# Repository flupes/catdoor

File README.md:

# catdoor
Cat door opening detection and notification

## First version

Notification of cat entry only (catdoor locked so that the cat can never go out, but always come in). This allows to make sure the cat in inside before dark in case we are coming late home.

### Sensing

Based on a proximity sensor looking down where the door opens. Some reflective on the side of the door allow a ver good signature, sorting out the cat. In fact, test of reflectivity on the cat hairs shows very poor reflection. Tuning the system as been done by observing serveral opening (look in the data directory)

- Microcontroller with ESP8266 Wifi:[Adafruit Feather HUZZAH with ESP8266 WiFi](https://www.adafruit.com/product/2821)
- Breadkout sensor board: [VCNL4010 Proximity/Light sensor](https://www.adafruit.com/product/466)

### Notification

The Feather HUZZAH sends a mqtt message to a Beagle Bone Black (BBB), which in turn sends notifications to a cell phone using Push Bullet.

The HUZZAH sends periodic updates of the door status, thus the BBB is can also detect potential anomalies.

This architecture with the HUZZAH + BBB never exposes the ESP8266 on the internet (only local communication).

## Second version

### Goals

- Outgoing locking mechanism that only allows the cat to go out during full daylight
- Notification of door actuation in the two direction (in and out)

Design ideas in ./design.md

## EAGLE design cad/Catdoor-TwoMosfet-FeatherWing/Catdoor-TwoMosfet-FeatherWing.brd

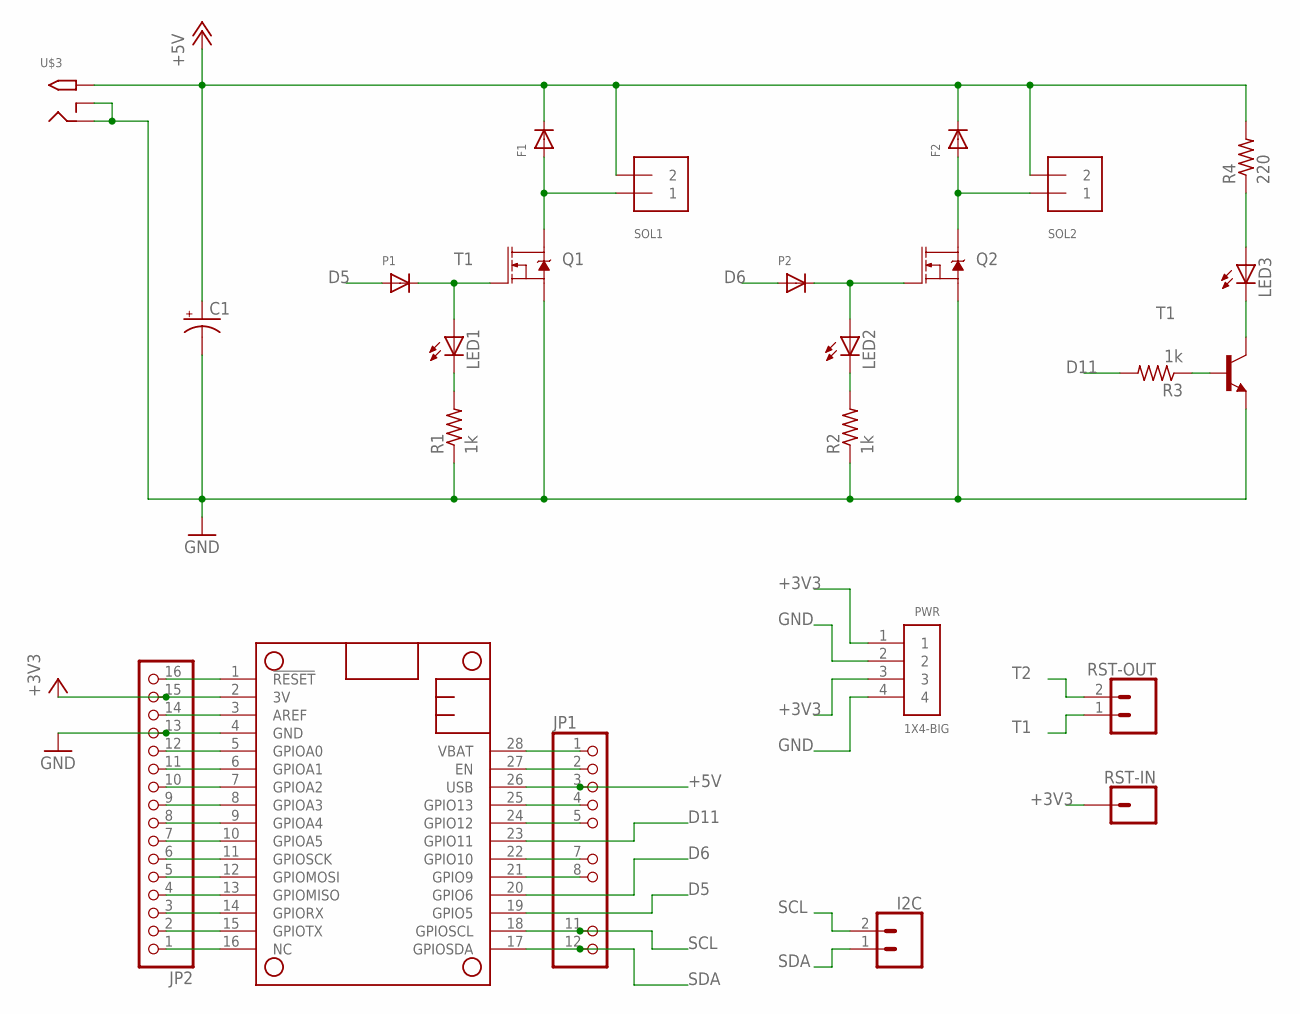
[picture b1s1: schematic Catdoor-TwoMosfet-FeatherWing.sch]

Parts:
C1: CPOL-USE5-13; E5-13
F1, F2: DIODELONG-SPACING; DIODE-LONG
I2C: CONN_02; 1X02
JP1: PINHD-1X12-CB; 1X12-CB
JP2: HEADER-1X16ROUND; 1X16_ROUND
LED1, LED2, LED3: LED3MM
MS1: FEATHERWING
P1, P2: DIODELONG-SPACING; DIODE-LONG
PWR: 1X4-BIG; 1X04-BIG
Q1, Q2: MOSFET-NCH-FQP30N06L; TO220V
R1, R2, R3: 1k; 0204/7
R4: 220; 0204/7
RST-IN: CONN_01; 1X01
RST-OUT: CONN_02; 1X02
SOL1, SOL2: TERMBLOCK_1X2; TERMBLOCK_1X2-3.5MM
T1: 2N2222; TO92-EBC-OVAL
U$3: 2.1MMJACKTHM; PJ-102A

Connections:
+3V3: JP2.15, MS1.2 (3V), PWR.1, PWR.3, RST-IN.1
+5V: C1.+, F1.C, F2.C, JP1.3, MS1.26 (USB), R4.2, SOL1.2, SOL2.2, U$3.TIP
D5: MS1.19 (GPIO5), P1.A
D6: MS1.20 (GPIO6), P2.A
D11: MS1.23 (GPIO11), R3.2
GND: C1.-, JP2.13, MS1.4 (GND), PWR.2, PWR.4, Q1.3 (S), Q2.3 (S), R1.1, R2.1, T1.E, U$3.RING, U$3.RING_SW
unnamed: JP1.2, MS1.27 (EN)
unnamed: JP1.4, MS1.25 (GPIO13)
unnamed: LED3.A, R4.1
unnamed: LED1.K (C), R1.2
unnamed: JP1.5, MS1.24 (GPIO12)
unnamed: LED3.K (C), T1.C
unnamed: R3.1, T1.B
unnamed: LED2.K (C), R2.2
unnamed: JP1.7, MS1.22 (GPIO10)
unnamed: JP1.8, MS1.21 (GPIO9)
unnamed: JP2.1, MS1.16 (NC)
unnamed: JP2.2, MS1.15 (GPIOTX)
unnamed: JP2.3, MS1.14 (GPIORX)
unnamed: JP2.4, MS1.13 (GPIOMISO)
unnamed: JP2.5, MS1.12 (GPIOMOSI)
unnamed: JP2.6, MS1.11 (GPIOSCK)
unnamed: JP2.7, MS1.10 (GPIOA5)
unnamed: JP2.8, MS1.9 (GPIOA4)
unnamed: JP2.9, MS1.8 (GPIOA3)
unnamed: JP2.10, MS1.7 (GPIOA2)
unnamed: JP2.11, MS1.6 (GPIOA1)
unnamed: JP2.12, MS1.5 (GPIOA0)
unnamed: JP2.14, MS1.3 (AREF)
unnamed: JP2.16, MS1.1 (!RESET)
S1: F1.A, Q1.2 (D), SOL1.1
S2: F2.A, Q2.2 (D), SOL2.1
SCL: I2C.2, JP1.11, MS1.18 (GPIOSCL)
SDA: I2C.1, JP1.12, MS1.17 (GPIOSDA)
T1: LED1.A, P1.C, Q1.1 (G), RST-OUT.1
T2: LED2.A, P2.C, Q2.1 (G), RST-OUT.2
VBAT: JP1.1, MS1.28 (VBAT)

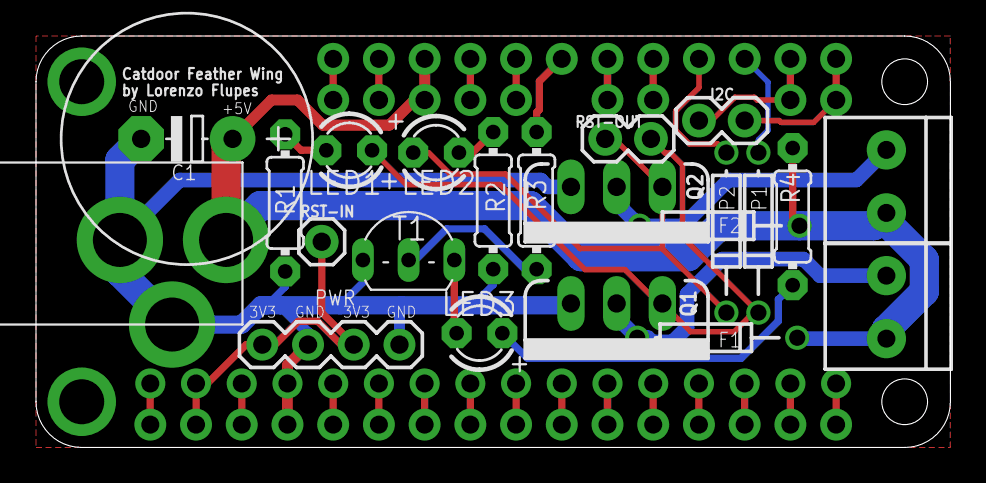
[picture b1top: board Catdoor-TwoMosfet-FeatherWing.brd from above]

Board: 2 copper layers, 50.8 x 22.9 mm, 25 parts (0 on the bottom side), 37 nets.

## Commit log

2016-11-20 first steps: detector and some eeprom utilities
2016-11-20 added an extra directory level because of the stupid Arduino IDE (need to go back to CMake)
2016-11-21 copied from google docs
2016-11-21 try to start formatting
2016-11-21 more formatting
2016-11-21 got formatting right
2016-11-21 some details about formatting
2016-11-21 follow the Arduino IDE constraints for the extra .ino programs
2016-11-21 updated after flashing a 3rd time...
2016-11-21 first state publisher: works only once...
2016-11-26 New version without the schedulers: Using Ticker was nicer, but caused occasional crashes. Exceptions (9) "Load or store to an # unaligned address" was triggered inside the Adafruit VCNL4010 (readPro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
2016-11-26 improved the logic for the mqtt client connection
2016-11-27 reboot the esp8266 after a number of client reconnect retries
2016-11-27 simple subscriber example to see how things are working (quite well in fact)
2016-11-27 first embryo of program with function and ~static variables
2016-11-27 started to encapsulate states in classes
2016-11-27 corrected typo introduced while changing the dead message
2016-11-27 proximity printer to record door signature
2016-11-27 more notes
2016-11-28 moved notes into subdir
2016-11-28 added recorded logs and analysis
2016-11-28 renamed in hope it will show up on github
2016-12-01 added Twilio SMS notification (very crude, works but no error checking)
2016-12-01 Push notification using Pushbutllet
2016-12-01 tuning the system
2016-12-05 added script to start the program in a tmux session
2016-12-05 added a systemd unit to start the catdoor system at boot
2017-05-15 started some documentation on the design
2017-05-18 wrote some more details
2017-07-18 refined some instructions
2017-07-24 added SolveSpace CAD file for solenoid mount
2017-07-30 added first test for solenoid actuation
2017-09-04 added modified Adafruit library for LIS3DH
2017-09-04 controls now 3 independant PWM (D5, D6 and D11)
2017-09-04 more tests
2017-09-04 added fritzing circuit for fun
2017-09-05 improved layout
2017-09-17 added second version of the circuit board (using Eagle)
2017-09-17 improved the silk screen
2017-09-18 version sent for fab
2017-09-24 ported the pure arduino project to atom/platformio
2017-11-05 working solution for proximity interrupts (but not cleaned yet)
2017-11-05 added a standalone proximity sensor test to ease debugging
2017-11-05 added individual accelerometer test
2017-11-05 re-organized the directory structure to share libraries between multiple main applications
2017-11-05 moved the tests from the main program to single apps
2017-11-05 force the pwm to zero at startup
2017-11-05 cleanup
2017-11-05 collected some data for analysis
2017-11-05 added instructions
2017-11-05 application with correct state machine
2017-11-06 added RTC, LED status and daylight control
2017-11-08 broke facilities in multiples files and fixed interrupt management
2017-11-08 added timing
2017-11-08 fixed threshold limitis
2017-11-08 added performance (timing of various hardware access) test
2017-11-08 publish the PWM signal traces
2017-11-08 new version of the app incorporating all the other fixes: seems to work much better
2017-11-11 added RTClib fork as submodule
2017-11-11 includes custom mods to RTClib
2017-11-11 added test program for the modified RTClib
2017-11-11 fence a little bit better the headers
2017-11-11 removed RTC wrapper since we use now a RTClib fork
2017-11-11 added sunrise and sunset times for San Francisco
2017-11-11 adapted to the new forked RTClib
2017-11-11 added a generator of a C table with sunrise and sunset times for one full year
2017-11-12 added more tests to understand the bad interaction of the RTC with the accelerometer
2017-11-12 fixed the state machine
2017-11-12 remove debugging statement
2017-11-12 provide hot release status
2017-11-12 added network stuff
2017-11-12 fixed some state machine, added battery monitoring and mqtt support
2017-11-12 pulse to not go down to zero
2017-11-12 added subscribers for catdoor v2 message
2017-11-12 adjusted install paths
2017-11-16 updated submodule
2017-11-16 re-organized to get clean dependencies
2017-11-16 added a watchdog timer functionality with LONG periods
2017-11-16 added watchdog safety to the main app
2017-11-16 added publisher test
2017-11-16 managed the LED in the background with a Timer(TC) + ISR and created and VisualFeedback interface
2017-11-16 adapted the test publisher to the re-worked mqtt wrapper
2017-11-16 simplified and improved the main app using the new mqtt wrapper, auto led update and VisualFeedback
2017-11-17 re-factored in clean/safe classes and made Solenoids state machine updated by the internal timer
2017-11-17 have the correct led DARK/DAYLIGH status restored correctly after a network outage
2017-11-18 lower ISR interrupt for LedCtrl + Solenoids and prepare for deployment
2017-11-18 changed state name for less confusion
2017-11-18 corrected the wifi connection routine
2017-11-18 added debug messages to step through the test
2017-11-18 adapted to the new Solenoids control and finalized the app
2017-11-18 subscribe to all new messages
2017-11-19 adapted program to new catdoor v2 states (this version will not work with the old catdoor)
2017-11-20 Added battery monitoring and time synchronization check
2017-11-20 tuned the threshold for the proximity sensor
2017-11-20 changed to declared the closed state only after some count
2017-11-20 Added a solenoid release condition if the cat is not well decided + some tuning
2017-11-20 increased the solenoid open max time based on some better experimentation
2017-11-20 captured some tuning of catdoor v1
2017-11-27 fixed bug in battery state analysis
2017-11-29 updated to work with the lates Accel class
2017-11-29 Try a calibration routine
2017-11-29 moved to a real angle based door position
2017-11-29 corrected include dependencies
2017-11-29 added debug information
2017-11-29 spin faster and adapted to new doorstate
2017-12-07 adjusted door angles
2017-12-07 improved test
2017-12-07 wait longer before unjamming
2018-04-30 updated build instructions
2018-05-03 made syntax compliant
2018-05-03 adjusted test to recents libraries
2018-05-03 take care to DST and adapted to new messages with time offset
2018-05-07 corrected dst correction ;-)
2018-09-27 RIP Misty :-( --- Welcome Luna
2018-09-27 fixed message string
2018-09-27 added typical instructions for mac
2018-09-27 increase the delay the cat can be out of view before releasing
2018-09-27 adjusted with the new parameters from the main app
2018-09-30 re-tuned the proximity sensor
2018-10-17 take more margin for Luna to get home, and rebuild with updated platform tools
2018-10-17 disable battery notifications and fixed LOCKED/UNLOCKED messages
2018-10-22 Use the same code for the test and the app. Initialization still not proper C++ practice
2018-12-02 started Catdoor Light: HW PWM servo control with feedback
2018-12-03 copy and simplified some libarries from v2
2018-12-03 prevent committing passwords by mistake
2018-12-09 added a simple pusher watching a file and a printer
2018-12-09 added an averaging feedback function
2018-12-09 added a simple test showing the analog feedback of the servo
2018-12-09 started real structure with mqtt and servo
2018-12-09 removed unused library (simplify)
2018-12-10 made the client work with python 3.x (need to decode bytes)
2018-12-10 servo responding to door master
2018-12-16 working board + master programs
2018-12-17 moved the mqtt app out of the way and try the adafruit.io rest API
2018-12-26 ore testing
2018-12-26 transformed to use adafruit IO

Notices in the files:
parts and their libraries:
microbuilder: This work is placed in the public domain, and may be freely used for commercial and non-commercial work with the following conditions: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
SparkFun-DiscreteSemi: Licensing: Creative Commons ShareAlike 4.0 International - https://creativecommons.org/licenses/by-sa/4.0
